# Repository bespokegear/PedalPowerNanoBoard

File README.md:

# PedalPowerNanoBoard
A simple break out board for the Arduino nano. Specifically designed for pedal powered projects.

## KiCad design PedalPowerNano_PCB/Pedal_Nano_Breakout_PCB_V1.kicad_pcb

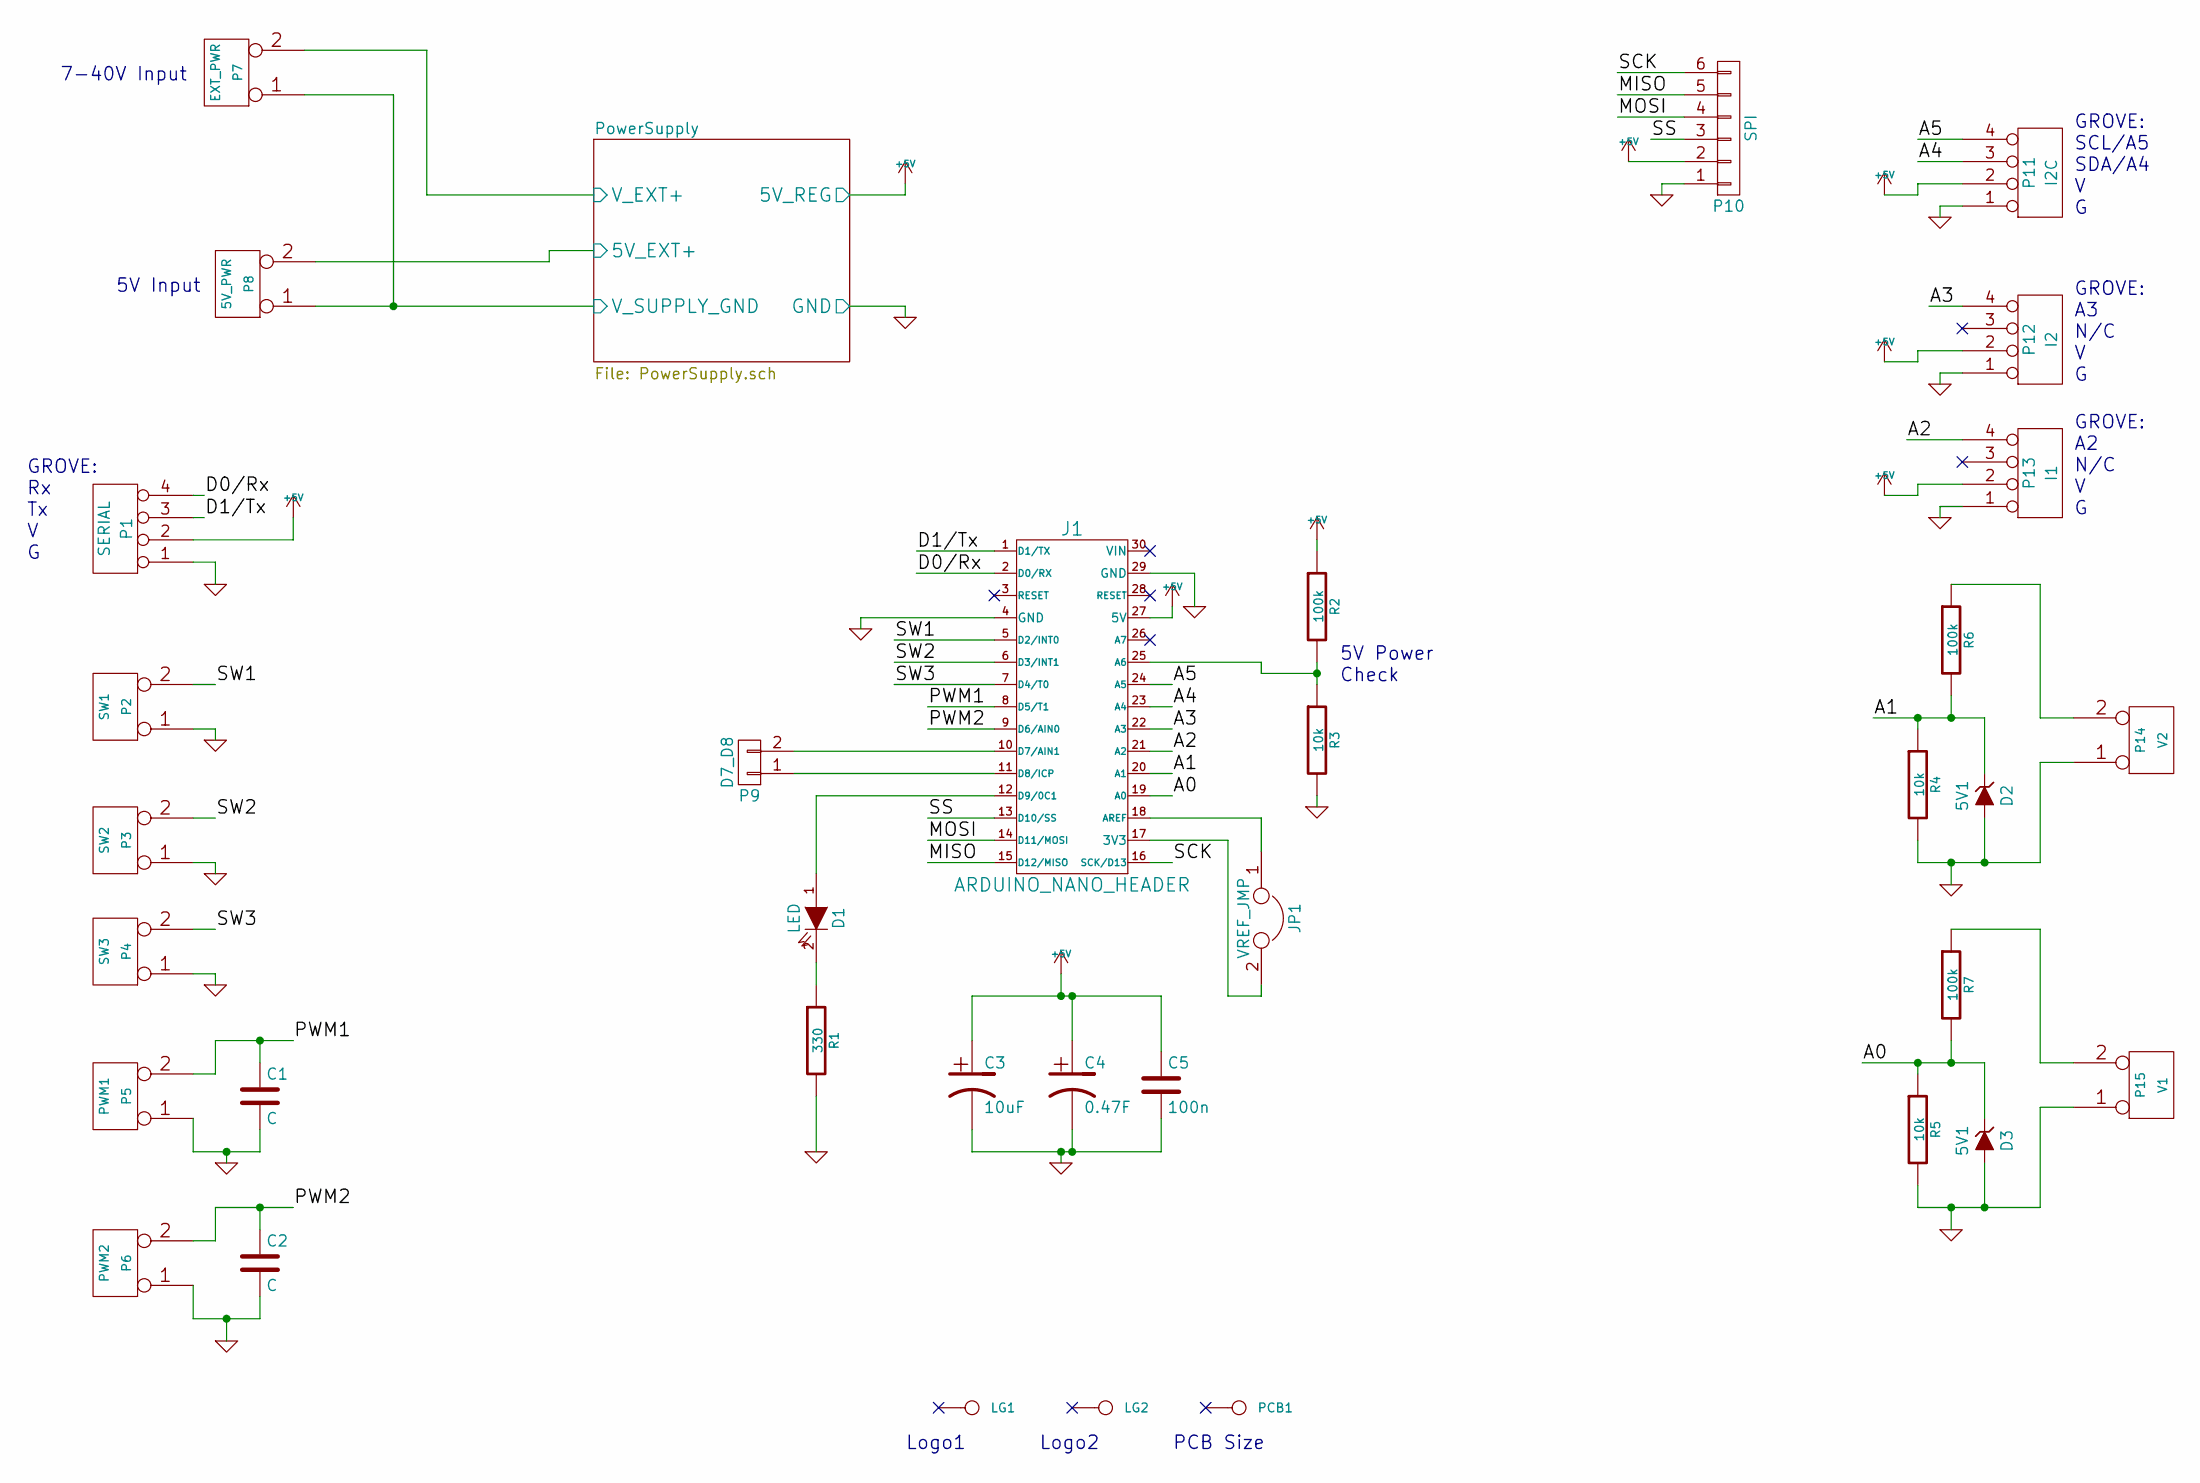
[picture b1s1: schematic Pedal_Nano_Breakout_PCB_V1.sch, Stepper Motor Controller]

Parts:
C1, C2: C; C1_wide_lg_pad
C3: 10uF; C_1V7_TH; Manufacturer Part No Value
C4: 0.47F; C_1F_SuperCap; Manufacturer Part No Value
C5: 100n; C1_wide_lg_pad
D1: LED; LED-5MM_larg_pad; Manufacturer Part No Value
D2, D3: 5V1; TH_Diode_1
J1: ARDUINO_NANO_HEADER; DIP_30_600_NANO
JP1: VREF_JMP; SIL-2_solder_connect
LG1: CONN_1; TCEC_Words_13mm
LG2: CONN_1; CuriousElectric_globe_10mm
P1: SERIAL; SIL-4_Grove_SCREW
P2: SW1; SIL-2_screw_terminal
P3: SW2; SIL-2_screw_terminal
P4: SW3; SIL-2_screw_terminal
P5: PWM1; SIL-2_screw_terminal
P6: PWM2; SIL-2_screw_terminal
P7: EXT_PWR; SIL-2_screw_terminal
P8: 5V_PWR; SIL-2_screw_terminal; Manufacturer Part No Value
P9: D7_D8; Pin_Header_Straight_1x02
P10: SPI; TH_6x1_CONN
P11: I2C; SIL-4_Grove_SIL
P12: I2; SIL-4_Grove_SIL
P13: I1; SIL-4_Grove_SIL
P14: V2; SIL-2_screw_terminal
P15: V1; SIL-2_screw_terminal
PCB1: CONN_1; PCB_50x100mm
R1: 330; TH_Resistor_1; Manufacturer Part No Value
R2, R6, R7: 100k; TH_Resistor_1; Manufacturer Part No Value
R3, R4, R5: 10k; TH_Resistor_1; Manufacturer Part No Value

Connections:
+5V: C3.1, C4.1, C5.1, J1.27 (5V), P1.2, P10.2, P11.2, P12.2, P13.2, R2.1; also elsewhere on the board
/A0: D3.2 (K), J1.19 (A0), R5.1, R7.2
/A1: D2.2 (K), J1.20 (A1), R4.1, R6.2
/A2: J1.21 (A2), P13.4
/A3: J1.22 (A3), P12.4
/A4: J1.23 (A4), P11.3
/A5: J1.24 (A5), P11.4
/D0/Rx: J1.2 (D0/RX), P1.4
/D1/Tx: J1.1 (D1/TX), P1.3
/MISO: J1.15 (D12/MISO), P10.5
/MOSI: J1.14 (D11/MOSI), P10.4
/PWM1: C1.1, J1.8 (D5/T1), P5.2 (PM)
/PWM2: C2.1, J1.9 (D6/AIN0), P6.2 (PM)
/PowerSupply/5V_EXT+: P8.2 (PM); also elsewhere on the board
/PowerSupply/V_EXT+: P7.2 (PM); also elsewhere on the board
/SCK: J1.16 (SCK/D13), P10.6
/SS: J1.13 (D10/SS), P10.3
/SW1: J1.5 (D2/INT0), P2.2 (PM)
/SW2: J1.6 (D3/INT1), P3.2 (PM)
/SW3: J1.7 (D4/T0), P4.2 (PM)
GND: C1.2, C2.2, C3.2, C4.2, C5.2, D2.1 (A), D3.1 (A), J1.4 (GND), J1.29 (GND), P1.1, P2.1, P3.1, P4.1, P5.1, P6.1, P7.1, P8.1, P10.1, P11.1, P12.1, P13.1, P14.1, P15.1, R1.2, R3.2, R4.2, R5.2; also elsewhere on the board
unnamed: D1.1 (A), J1.12 (D9/0C1)
unnamed: D1.2 (K), R1.1
unnamed: J1.10 (D7/AIN1), P9.2
unnamed: J1.11 (D8/ICP), P9.1
unnamed: J1.17 (3V3), JP1.2
unnamed: J1.18 (AREF), JP1.1
unnamed: J1.25 (A6), R2.2, R3.1
unnamed: P14.2 (PM), R6.1
unnamed: P15.2 (PM), R7.1

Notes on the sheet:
PCB Size
GROVE: Rx Tx V G
GROVE: SCL/A5 SDA/A4 V G
5V Power Check
GROVE: A3 N/C V G
GROVE: A2 N/C V G
7-40V Input
5V Input
Logo2
Logo1

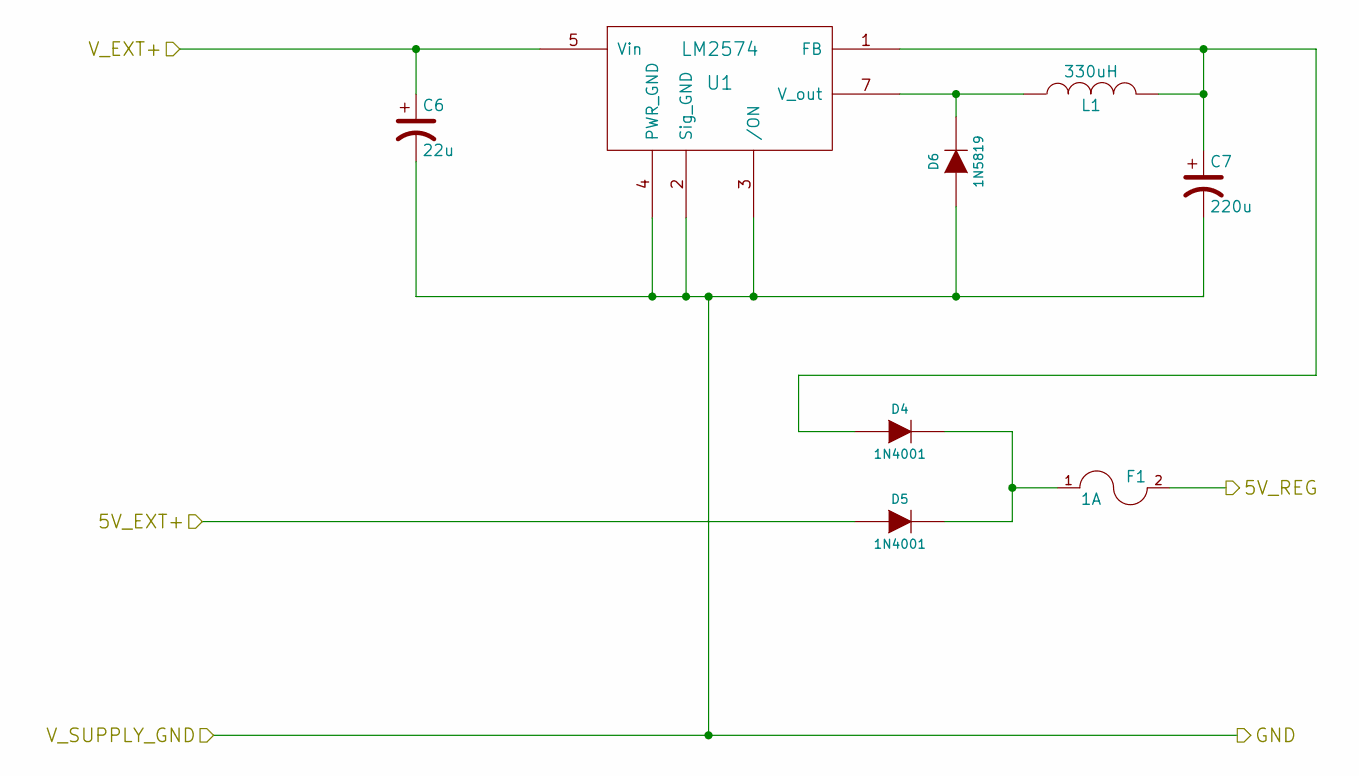
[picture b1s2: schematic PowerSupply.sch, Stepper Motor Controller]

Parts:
C6: 22u; C_1V7_TH
C7: 220u; C_1V7_TH
D4, D5: 1N4001; TH_Diode_1
D6: 1N5819; TH_Diode_1
F1: 1A; TH_MC36188_FUSE
L1: 330uH; TH_Inductor
U1: LM2574; DIP-8_300_ELL

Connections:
+5V: F1.2; also elsewhere on the board
/PowerSupply/5V_EXT+: D5.1 (A); also elsewhere on the board
/PowerSupply/V_EXT+: C6.1, U1.5 (Vin); also elsewhere on the board
GND: C6.2, C7.2, D6.1 (A), U1.2 (Sig_GND), U1.3 (/ON), U1.4 (PWR_GND); also elsewhere on the board
unnamed: C7.1, D4.1 (A), L1.2, U1.1 (FB)
unnamed: D4.2 (K), D5.2 (K), F1.1
unnamed: D6.2 (K), L1.1, U1.7 (V_out)

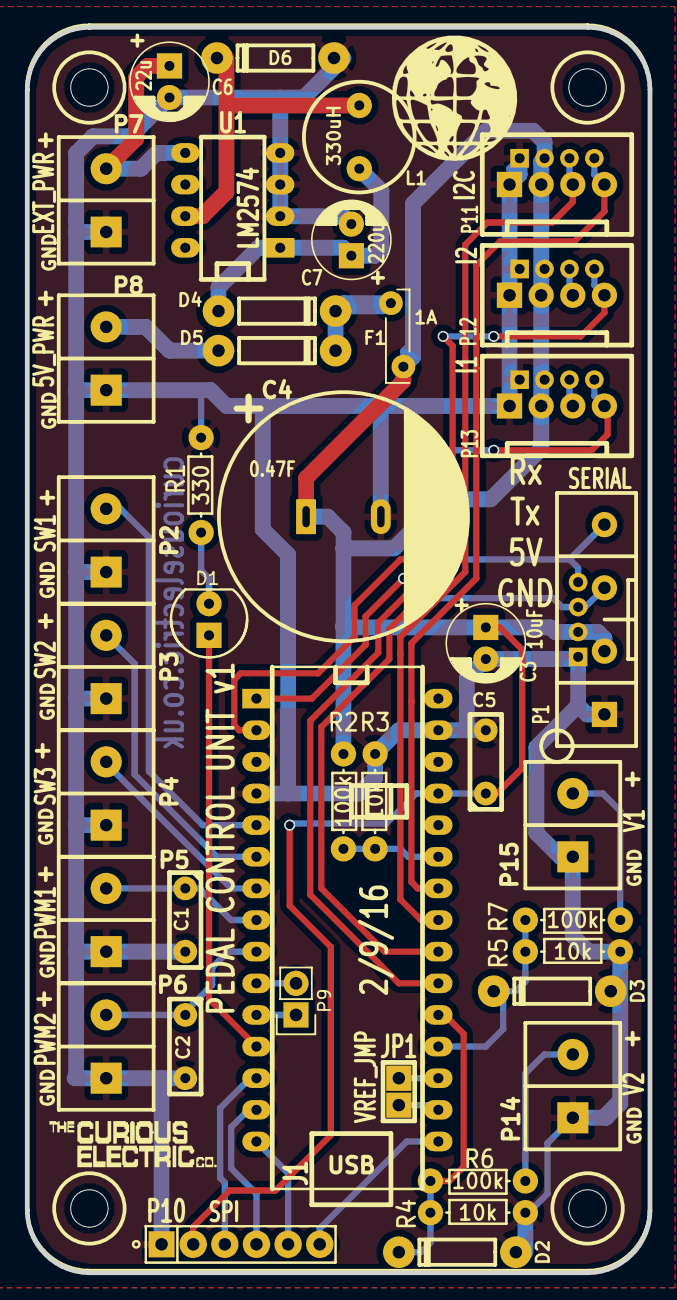
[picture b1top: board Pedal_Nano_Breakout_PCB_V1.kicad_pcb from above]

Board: 2 copper layers, 50.0 x 100.0 mm, 43 parts (0 on the bottom side), 33 nets.

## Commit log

2017-04-19 First commit of PCB design
2018-12-30 Update PCB
